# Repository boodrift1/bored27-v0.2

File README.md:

# bored27-v0.2
*WARNING: This PCB has not been tested and there is currently no firmware available for it.

bored27 - 27 key PCB inspired by flurples' cardboard keyboard: https://www.youtube.com/watch?v=sVInBOLSqoM <br />
designed for use with plate provided in original video description

changes from v0.1: <br />
moved diodes to front (inspired by mode designs' pcbs) <br />
changed from atmega32u4 to atmega32u2 (less components, simpler, cheaper)

designed w/ kicad

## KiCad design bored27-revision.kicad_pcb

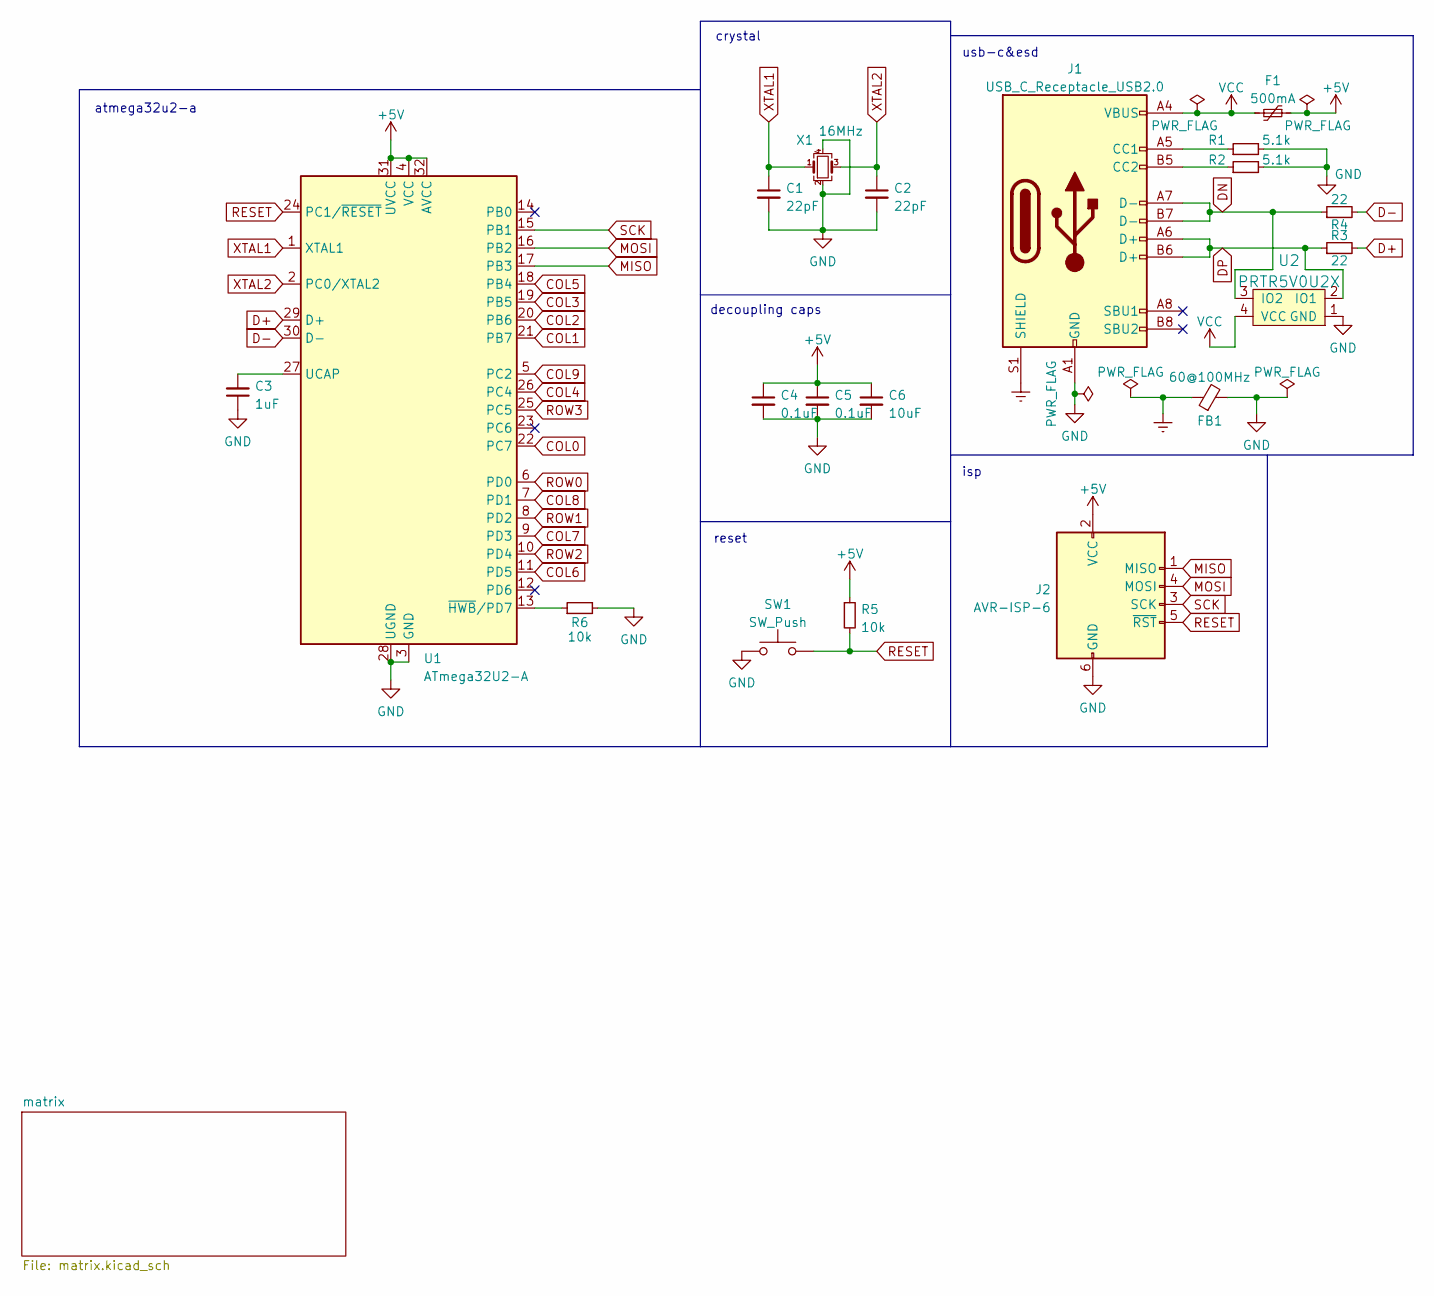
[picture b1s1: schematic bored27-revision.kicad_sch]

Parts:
C1, C2: 22pF; C_0805_2012Metric_Pad1.18x1.45mm_HandSolder
C3: 1uF; C_0805_2012Metric_Pad1.18x1.45mm_HandSolder
C4, C5: 0.1uF; C_0805_2012Metric_Pad1.18x1.45mm_HandSolder
C6: 10uF; C_0805_2012Metric_Pad1.18x1.45mm_HandSolder
F1: 500mA; Fuse_1206_3216Metric_Pad1.42x1.75mm_HandSolder
FB1: 60@100MHz; L_0805_2012Metric_Pad1.15x1.40mm_HandSolder
J1: USB_C_Receptacle_USB2.0; USB_C_Receptacle_HRO_TYPE-C-31-M-12
J2: AVR-ISP-6; Reset_Pretty-Mask
R1, R2: 5.1k; R_0805_2012Metric_Pad1.20x1.40mm_HandSolder
R3, R4: 22; R_0805_2012Metric_Pad1.20x1.40mm_HandSolder
R5, R6: 10k; R_0805_2012Metric_Pad1.20x1.40mm_HandSolder
SW1: SW_Push; SW_SPST_SKQG_WithStem
U1: ATmega32U2-A; TQFP-32_7x7mm_P0.8mm
U2: PRTR5V0U2X; SOT143B
X1: 16MHz; Crystal_SMD_3225-4Pin_3.2x2.5mm_HandSoldering

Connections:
+5V: C4.1, C5.1, C6.1, F1.1, J2.2 (VCC), R5.1, U1.4 (VCC), U1.31 (UVCC), U1.32 (AVCC)
COL0: U1.22 (PC7); also elsewhere on the board
COL1: U1.21 (PB7); also elsewhere on the board
COL2: U1.20 (PB6); also elsewhere on the board
COL3: U1.19 (PB5); also elsewhere on the board
COL4: U1.26 (PC4); also elsewhere on the board
COL5: U1.18 (PB4); also elsewhere on the board
COL6: U1.11 (PD5); also elsewhere on the board
COL7: U1.9 (PD3); also elsewhere on the board
COL8: U1.7 (PD1); also elsewhere on the board
COL9: U1.5 (PC2); also elsewhere on the board
D+: R3.2, U1.29 (D+)
D-: R4.2, U1.30 (D-)
DN: J1.A7 (D-), J1.B7 (D-), R4.1, U2.3 (IO2)
DP: J1.A6 (D+), J1.B6 (D+), R3.1, U2.2 (IO1)
Earth: FB1.1, J1.S1 (SHIELD)
GND: C1.2, C2.2, C3.1, C4.2, C5.2, C6.2, FB1.2, J1.A1 (GND), J1.A12 (GND), J1.B1 (GND), J1.B12 (GND), J2.6 (GND), R1.2, R2.2, R6.2, SW1.1, U1.3 (GND), U1.28 (UGND), U2.1 (GND), X1.2, X1.4
MISO: J2.1 (MISO), U1.17 (PB3)
MOSI: J2.4 (MOSI), U1.16 (PB2)
unnamed: C3.2, U1.27 (UCAP)
unnamed: J1.A5 (CC1), R1.1
unnamed: J1.B5 (CC2), R2.1
unnamed: R6.1, U1.13 (~HWB/PD7)
RESET: J2.5 (~RST), R5.2, SW1.2, U1.24 (PC1/~RESET)
ROW0: U1.6 (PD0); also elsewhere on the board
ROW1: U1.8 (PD2); also elsewhere on the board
ROW2: U1.10 (PD4); also elsewhere on the board
ROW3: U1.25 (PC5); also elsewhere on the board
SCK: J2.3 (SCK), U1.15 (PB1)
VCC: F1.2, J1.A4 (VBUS), J1.A9 (VBUS), J1.B4 (VBUS), J1.B9 (VBUS), U2.4 (VCC)
XTAL1: C1.1, U1.1 (XTAL1), X1.1
XTAL2: C2.1, U1.2 (PC0/XTAL2), X1.3

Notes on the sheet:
crystal
usb-c&esd
decoupling caps
atmega32u2-a
isp
reset

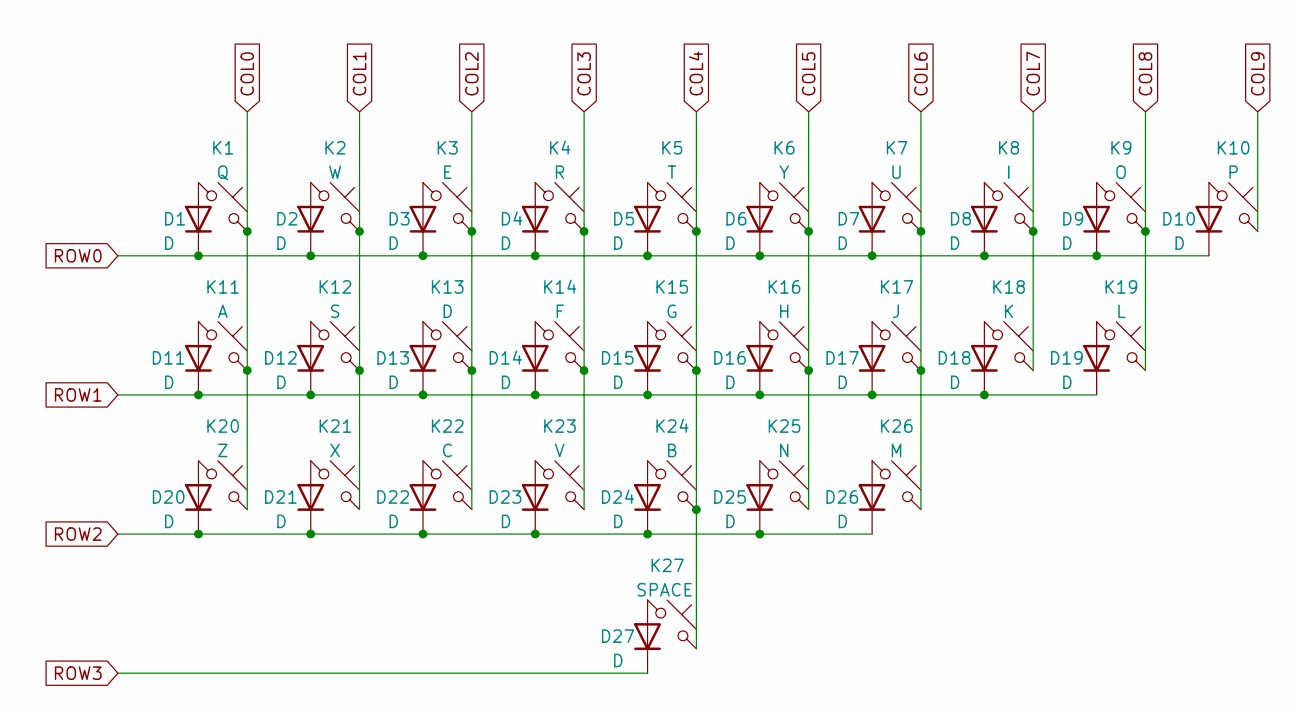
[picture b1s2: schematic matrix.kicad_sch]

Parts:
D1, D2, D3, D4, D5, D6, D7, D8, D9, D10, D11, D12, D13, D14, D15, D16, D17, D18, D19, D20, D21, D22, D23, D24, D25, D26, D27: D; D_SOD-123
K1: Q; SW_MX_HS_1u
K2: W; SW_MX_HS_1u
K3: E; SW_MX_HS_1u
K4: R; SW_MX_HS_1u
K5: T; SW_MX_HS_1u
K6: Y; SW_MX_HS_1u
K7: U; SW_MX_HS_1u
K8: I; SW_MX_HS_1u
K9: O; SW_MX_HS_1u
K10: P; SW_MX_HS_1u
K11: A; SW_MX_HS_1u
K12: S; SW_MX_HS_1u
K13: D; SW_MX_HS_1u
K14: F; SW_MX_HS_1u
K15: G; SW_MX_HS_1u
K16: H; SW_MX_HS_1u
K17: J; SW_MX_HS_1u
K18: K; SW_MX_HS_1u
K19: L; SW_MX_HS_1u
K20: Z; SW_MX_HS_1u
K21: X; SW_MX_HS_1u
K22: C; SW_MX_HS_1u
K23: V; SW_MX_HS_1u
K24: B; SW_MX_HS_1u
K25: N; SW_MX_HS_1u
K26: M; SW_MX_HS_1u
K27: SPACE; SW_MX_HS_1u

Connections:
COL0: K1.2, K11.2, K20.2; also elsewhere on the board
COL1: K2.2, K12.2, K21.2; also elsewhere on the board
COL2: K3.2, K13.2, K22.2; also elsewhere on the board
COL3: K4.2, K14.2, K23.2; also elsewhere on the board
COL4: K5.2, K15.2, K24.2, K27.2; also elsewhere on the board
COL5: K6.2, K16.2, K25.2; also elsewhere on the board
COL6: K7.2, K17.2, K26.2; also elsewhere on the board
COL7: K8.2, K18.2; also elsewhere on the board
COL8: K9.2, K19.2; also elsewhere on the board
COL9: K10.2; also elsewhere on the board
unnamed: D1.2 (A), K1.1
unnamed: D2.2 (A), K2.1
unnamed: D3.2 (A), K3.1
unnamed: D4.2 (A), K4.1
unnamed: D5.2 (A), K5.1
unnamed: D6.2 (A), K6.1
unnamed: D7.2 (A), K7.1
unnamed: D8.2 (A), K8.1
unnamed: D9.2 (A), K9.1
unnamed: D10.2 (A), K10.1
unnamed: D11.2 (A), K11.1
unnamed: D12.2 (A), K12.1
unnamed: D13.2 (A), K13.1
unnamed: D14.2 (A), K14.1
unnamed: D15.2 (A), K15.1
unnamed: D16.2 (A), K16.1
unnamed: D17.2 (A), K17.1
unnamed: D18.2 (A), K18.1
unnamed: D19.2 (A), K19.1
unnamed: D20.2 (A), K20.1
unnamed: D21.2 (A), K21.1
unnamed: D22.2 (A), K22.1
unnamed: D23.2 (A), K23.1
unnamed: D24.2 (A), K24.1
unnamed: D25.2 (A), K25.1
unnamed: D26.2 (A), K26.1
unnamed: D27.2 (A), K27.1
ROW0: D1.1 (K), D2.1 (K), D3.1 (K), D4.1 (K), D5.1 (K), D6.1 (K), D7.1 (K), D8.1 (K), D9.1 (K), D10.1 (K); also elsewhere on the board
ROW1: D11.1 (K), D12.1 (K), D13.1 (K), D14.1 (K), D15.1 (K), D16.1 (K), D17.1 (K), D18.1 (K), D19.1 (K); also elsewhere on the board
ROW2: D20.1 (K), D21.1 (K), D22.1 (K), D23.1 (K), D24.1 (K), D25.1 (K), D26.1 (K); also elsewhere on the board
ROW3: D27.1 (K); also elsewhere on the board

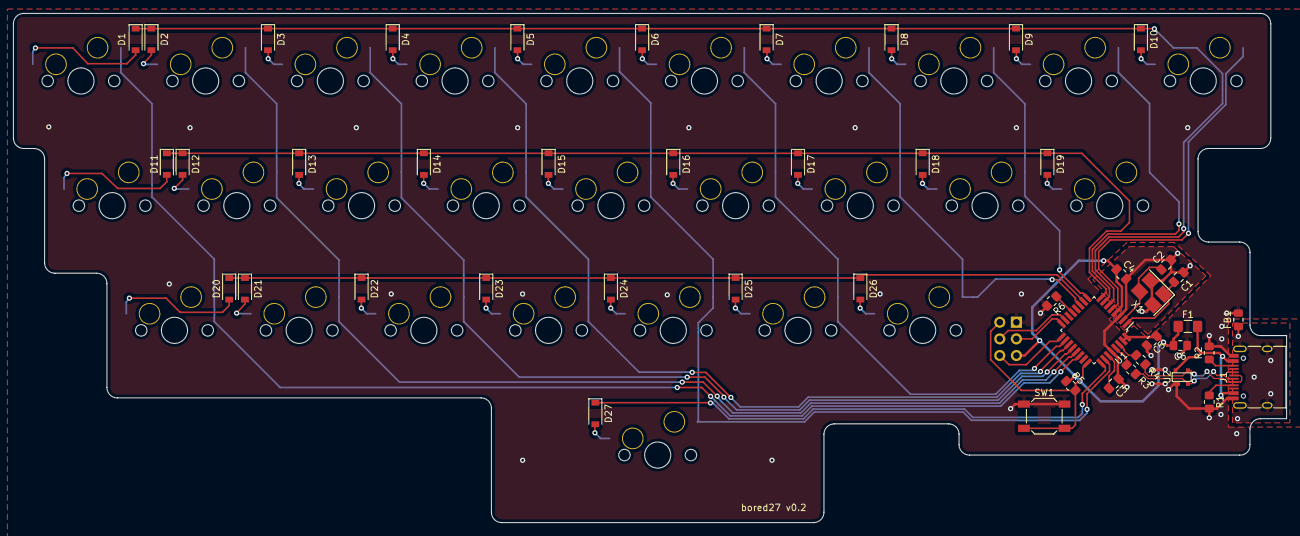
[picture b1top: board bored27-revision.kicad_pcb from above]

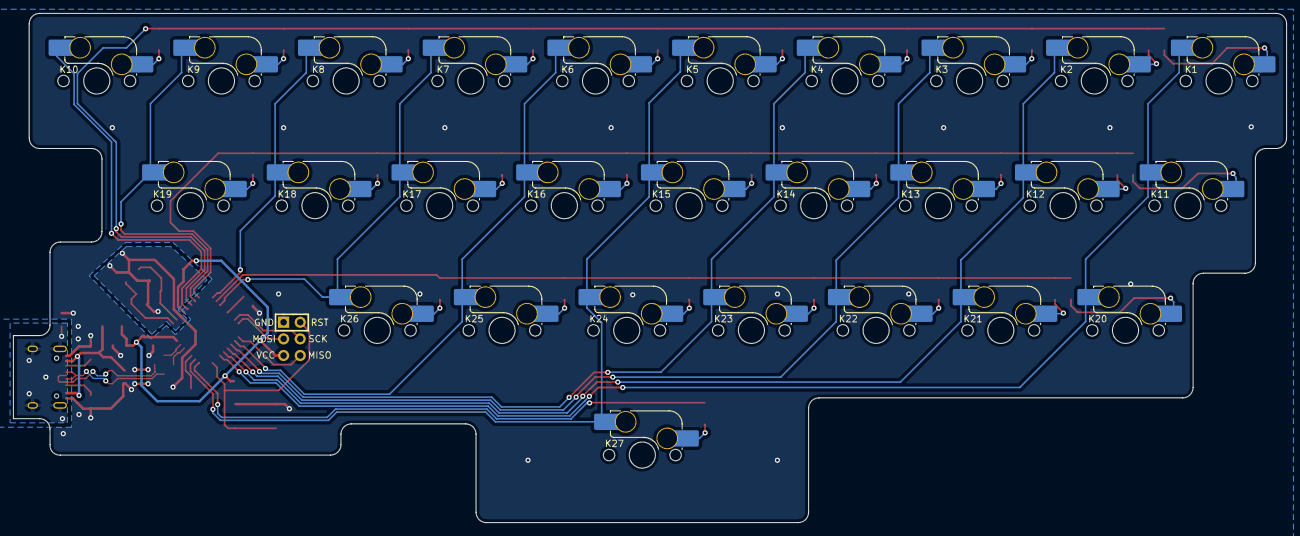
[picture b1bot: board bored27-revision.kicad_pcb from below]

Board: 2 copper layers, 194.5 x 77.8 mm, 74 parts (28 on the bottom side), 59 nets.

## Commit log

2022-08-04 initializing project
2022-08-04 i screwed up with the files AAAAA
2022-08-04 adding submodules
2022-08-04 adding libraries
2022-08-05 mostly finished schematic
2022-08-05 beginning pcb
2022-08-05 placement of pcb components
2022-08-06 finished pcb
2022-08-06 generated gerber files
2022-08-06 generated csv file
2022-08-06 autosave
